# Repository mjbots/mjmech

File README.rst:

======
mjmech
======

Source and design files for various walking robots, their controlling
interfaces, and utilities for developing and operating them.

* GitHub https://github.com/mjbots/mjmech
* Most files are free hardware and software: Apache 2.0 License

Directory structure
===================

 * **base/** - C++ source files common to many applications.
 * **mech/** - C++ source files specific to walking robots.
 * **python/** - Python bindings for various C++ classes.
 * **legtool/** - A python application for experimenting with static
   walking gaits.
 * **tools/** - Utilities for development and data analysis.
 * **video-ui/** - Client application for FPV and real-time control.
 * **configs/** - Configuration files for different robots and applications.
 * **hw/** - Hardware design files along with firmware.

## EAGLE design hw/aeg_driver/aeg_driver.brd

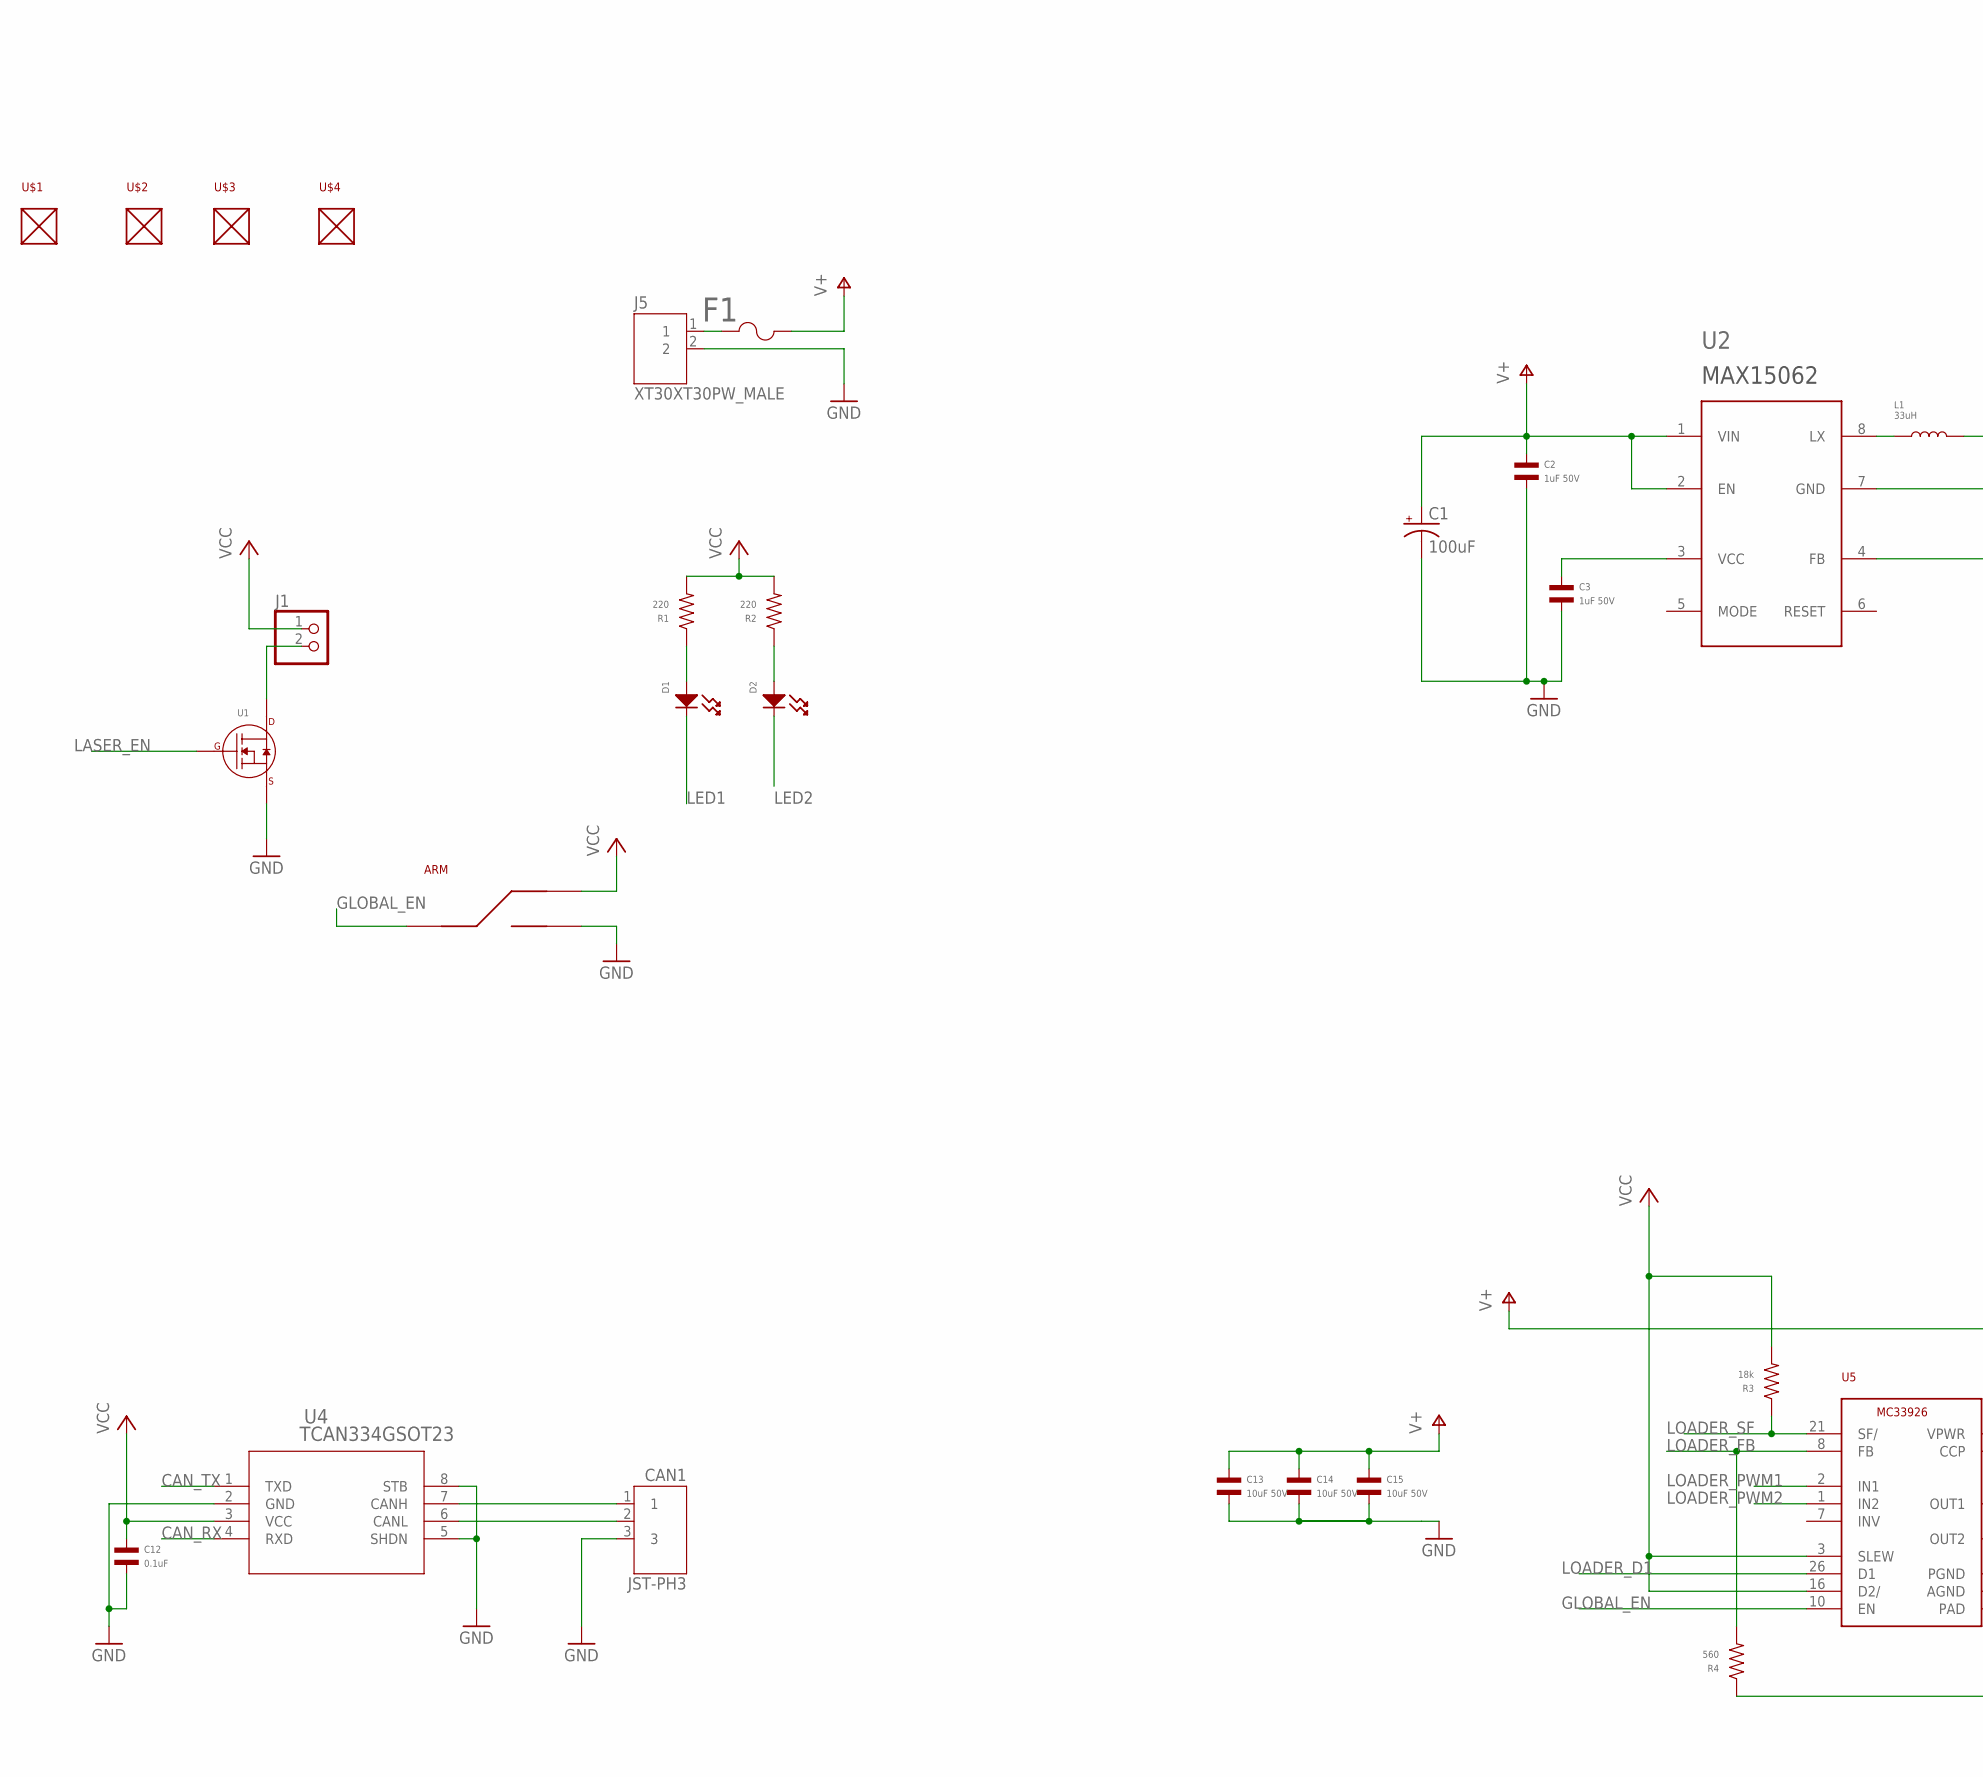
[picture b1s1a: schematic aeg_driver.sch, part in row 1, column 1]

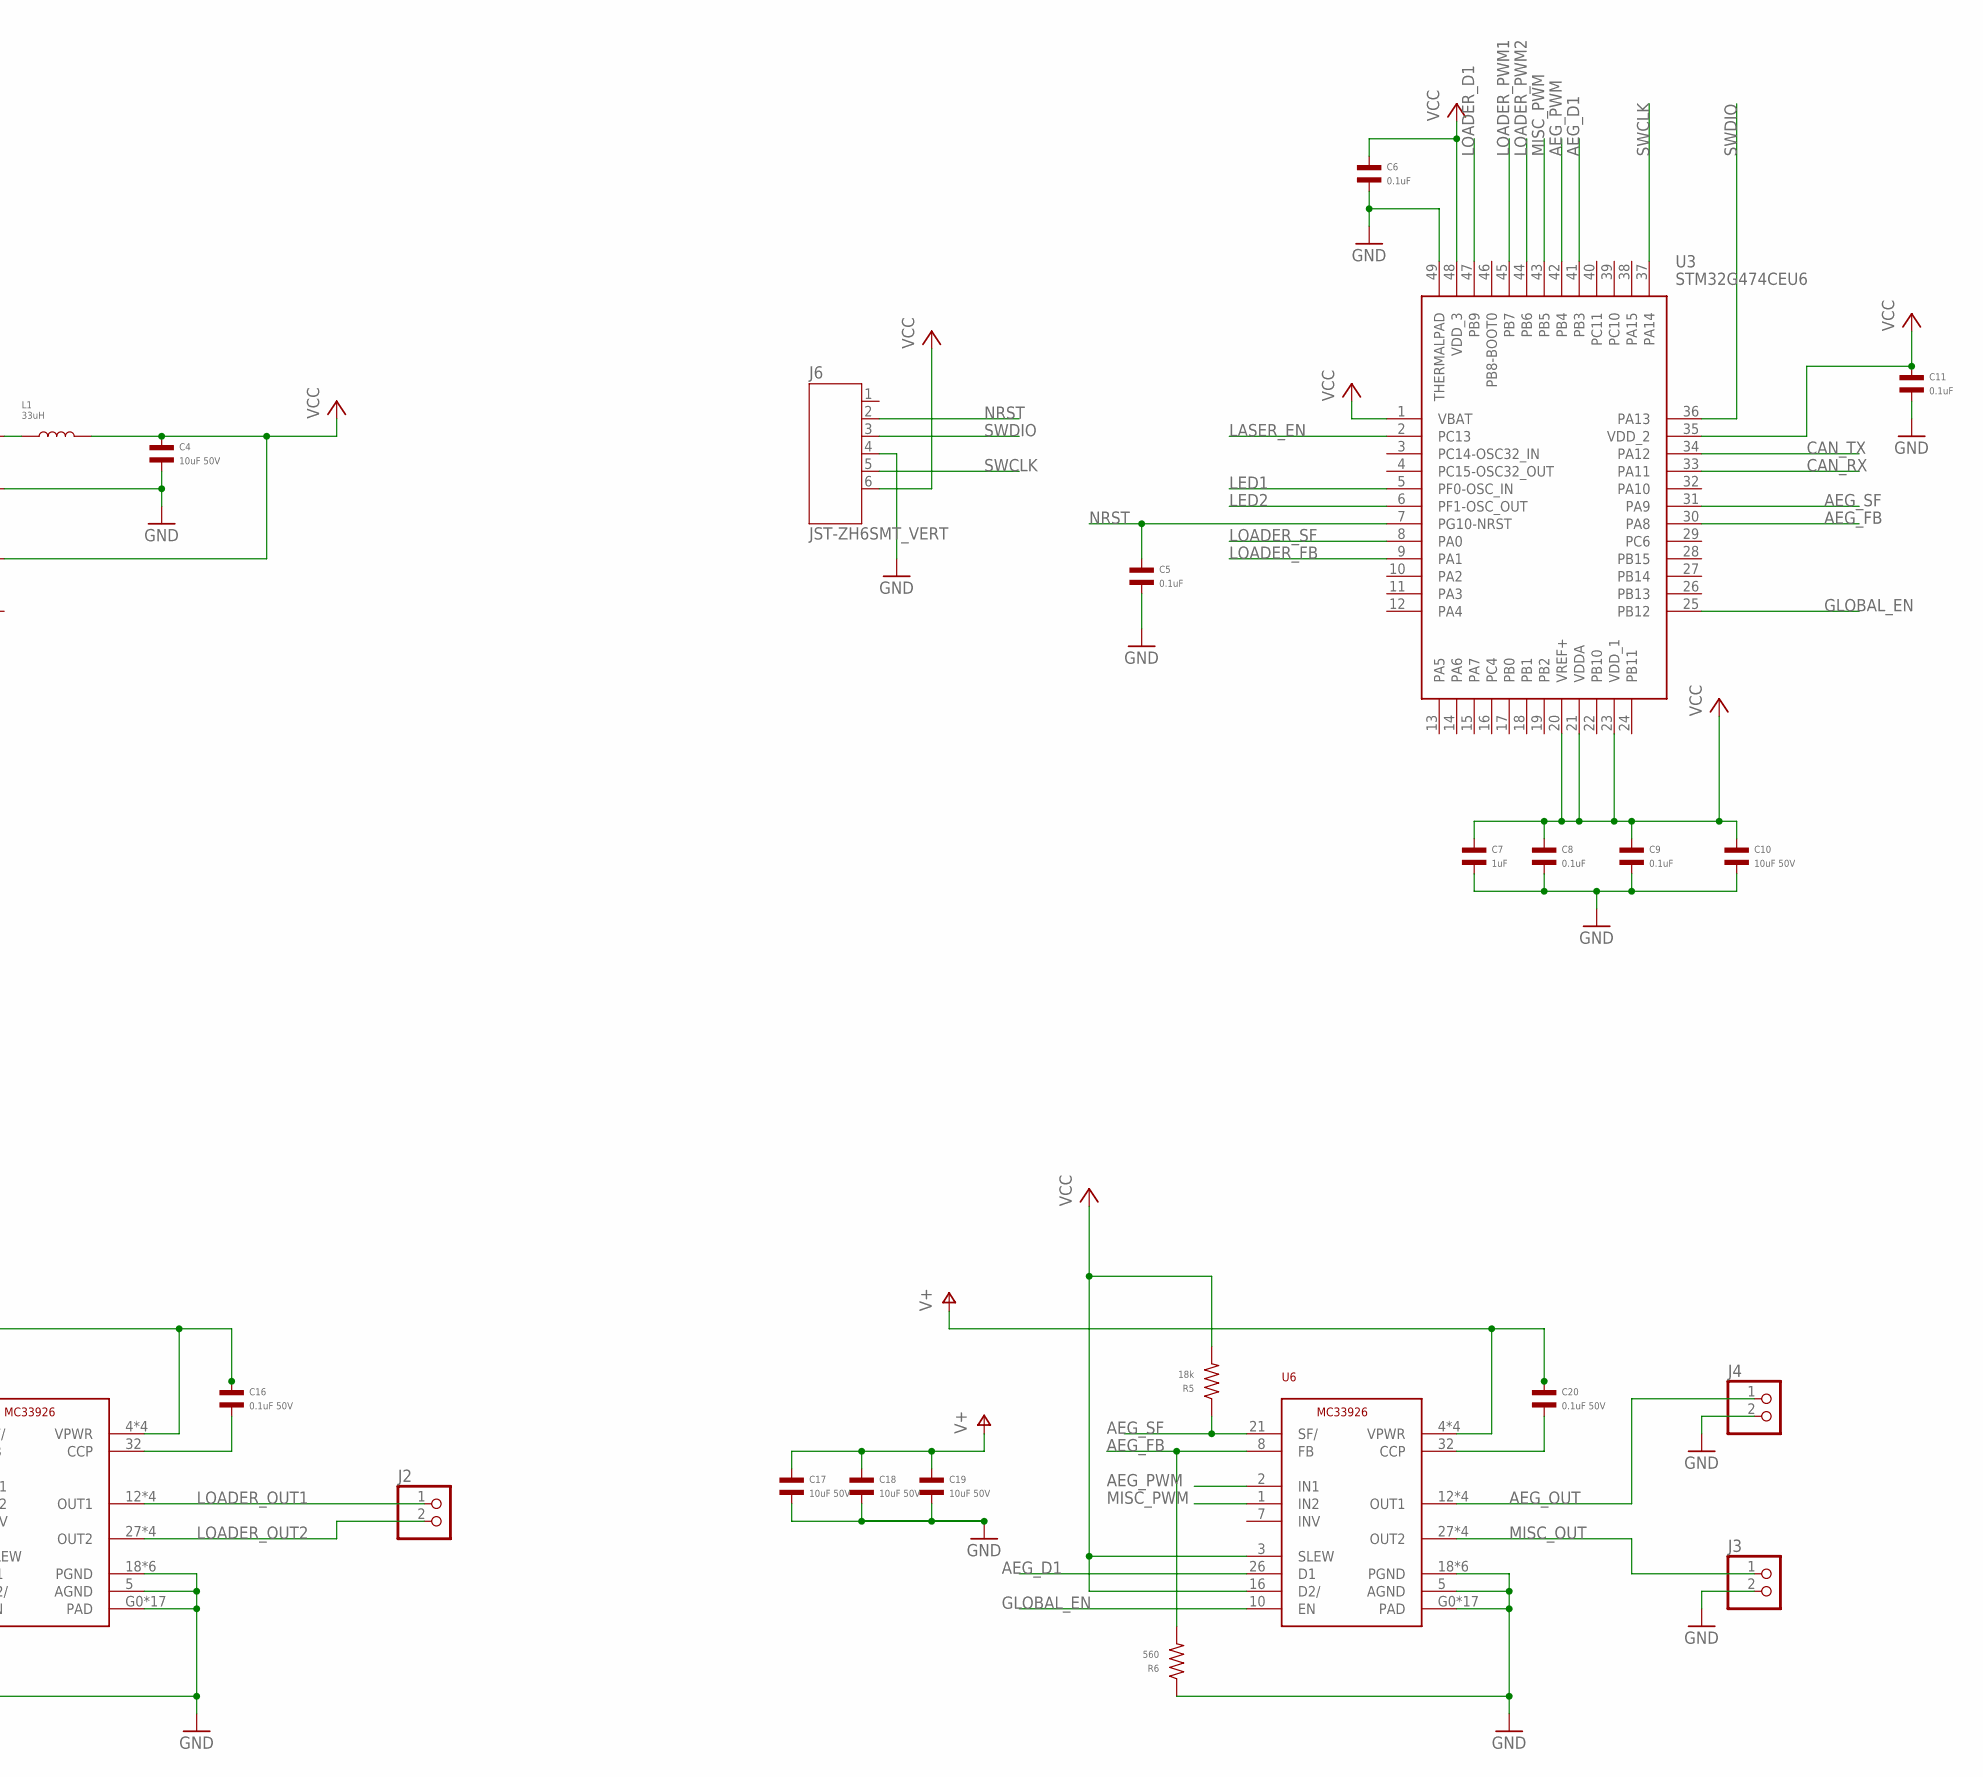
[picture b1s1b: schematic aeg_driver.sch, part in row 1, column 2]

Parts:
ARM: SLIDE_SWITCHJS_SUB_SWITCH; JS_SUB_SWITCH; MPN JS102011SAQN
C1: 100uF; PANASONIC_FT_CAP_D; MPN EEE-FT1V101AP
C2, C3: 1uF 50V; C0603; MPN CL10A105KB8NNNC
C4, C10, C13, C14, C15, C17, C18, C19: 10uF 50V; C1206; MPN C3216X7R1H106K160AE
C5, C6, C8, C9, C11, C12: 0.1uF; C0402; MPN MF-CAP-0402-0.1uF
C7: 1uF; C0402; MPN MF-CAP-0402-1uF
C16, C20: 0.1uF 50V; C0402; MPN 0402B104K500CT
CAN1: JST-PH3; JST_S3B-PH-SM4-TB(LF)(SN); MPN S3B-PH-SM4-TB(LF)(SN)
D1: LED_SINGLE-0603-RED; LED0603
D2: LED_SINGLE-0603-RED; LED0603; MPN MF-LED-0603-GREEN
F1: MFU0603FF04000P100; FUS_VISHAY_MFU0603; MPN MFU0603FF04000P100
J1, J2, J3, J4: PINHD-1X2; 1X02
J5: XT30XT30PW_MALE; XT30PW_MALE; MPN XT30PW-M
J6: JST-ZH6SMT_VERT; JST_B6B-ZR-SM4-TF(LF)(SN); MPN B6B-ZR-SM4-TF(LF)(SN)
L1: 33uH; L1210; MPN NLFV32T-330K-EF
R1, R2: 220; R0603; MPN MF-RES-0603-220
R3, R5: 18k; R0603; MPN MF-RES-0603-18K
R4, R6: 560; R0603; MPN MF-RES-0603-560
U1: N-CHANNEL_FET_SOT-23-3; SOT-23-3; MPN MF-DSC-SOT233-BSS138
U2: MAX150628TDFN; 8TDFN; MPN MAX15062AATA+T
U3: STM32G474CEU6; QFN50P700X700X60-49N; MPN STM32G474CEU6
U4: TCAN334GSOT23; SOT23-8; MPN TCAN334GDCNT
U5, U6: MC33926; PQFN32; MPN MC33926PNBR2
U$1, U$2, U$3, U$4: MOUNT; M2.5MOUNT

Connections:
AEG_D1: U3.41 (PB3), U6.26 (D1)
AEG_FB: R6.P$2, U3.30 (PA8), U6.8 (FB)
AEG_OUT: J4.1, U6.12 (OUT1), U6.13 (OUT1), U6.14 (OUT1), U6.15 (OUT1)
AEG_PWM: U3.42 (PB4), U6.2 (IN1)
AEG_SF: R5.P$1, U3.31 (PA9), U6.21 (SF/)
CAN_N: CAN1.2, U4.6 (CANL)
CAN_P: CAN1.1, U4.7 (CANH)
CAN_RX: U3.33 (PA11), U4.4 (RXD)
CAN_TX: U3.34 (PA12), U4.1 (TXD)
GLOBAL_EN: ARM.2, U3.25 (PB12), U5.10 (EN), U6.10 (EN)
GND: ARM.3, C1.-, C2.P$2, C3.P$2, C4.P$2, C5.P$2, C6.P$2, C7.P$2, C8.P$2, C9.P$2, C10.P$2, C11.P$2, C12.P$2, C13.P$2, C14.P$2, C15.P$2, C17.P$2, C18.P$2, C19.P$2, CAN1.3, J3.2, J4.2, J5.2, J6.4, R4.P$1, R6.P$1, U1.P$2 (SOURCE), U2.7 (GND), U3.49 (THERMALPAD), U4.2 (GND), U4.5 (SHDN), U4.8 (STB), U5.5 (AGND), U5.18 (PGND), U5.19 (PGND), U5.20 (PGND), U5.22 (PGND), U5.23 (PGND), U5.24 (PGND), U5.G0 (PAD), U5.G1 (PAD), U5.G2 (PAD), U5.G3 (PAD), U5.G4 (PAD), U5.G5 (PAD), U5.G6 (PAD), U5.G7 (PAD), U5.G8 (PAD), U5.G9 (PAD), U5.G10 (PAD), U5.G11 (PAD), U5.G12 (PAD), U5.G13 (PAD), U5.G14 (PAD), U5.G15 (PAD), U5.G16 (PAD), U6.5 (AGND), U6.18 (PGND), U6.19 (PGND), U6.20 (PGND), U6.22 (PGND), U6.23 (PGND), U6.24 (PGND), U6.G0 (PAD), U6.G1 (PAD), U6.G2 (PAD), U6.G3 (PAD), U6.G4 (PAD), U6.G5 (PAD), U6.G6 (PAD), U6.G7 (PAD), U6.G8 (PAD), U6.G9 (PAD), U6.G10 (PAD), U6.G11 (PAD), U6.G12 (PAD), U6.G13 (PAD), U6.G14 (PAD), U6.G15 (PAD), U6.G16 (PAD)
LASER_EN: U1.P$1 (GATE), U3.2 (PC13)
LED1: D1.CATHODE, U3.5 (PF0-OSC_IN)
LED2: D2.CATHODE, U3.6 (PF1-OSC_OUT)
LOADER_D1: U3.47 (PB9), U5.26 (D1)
LOADER_FB: R4.P$2, U3.9 (PA1), U5.8 (FB)
LOADER_OUT1: J2.1, U5.12 (OUT1), U5.13 (OUT1), U5.14 (OUT1), U5.15 (OUT1)
LOADER_OUT2: J2.2, U5.27 (OUT2), U5.28 (OUT2), U5.29 (OUT2), U5.30 (OUT2)
LOADER_PWM1: U3.45 (PB7), U5.2 (IN1)
LOADER_PWM2: U3.44 (PB6), U5.1 (IN2)
LOADER_SF: R3.P$1, U3.8 (PA0), U5.21 (SF/)
LX: L1.P$1, U2.8 (LX)
MISC_OUT: J3.1, U6.27 (OUT2), U6.28 (OUT2), U6.29 (OUT2), U6.30 (OUT2)
MISC_PWM: U3.43 (PB5), U6.1 (IN2)
unnamed: C20.P$2, U6.32 (CCP)
unnamed: J1.2, U1.P$3 (DRAIN)
unnamed: F1.1, J5.1
unnamed: C16.P$2, U5.32 (CCP)
unnamed: C3.P$1, U2.3 (VCC)
unnamed: D1.ANODE, R1.P$1
unnamed: D2.ANODE, R2.P$1
NRST: C5.P$1, J6.2, U3.7 (PG10-NRST)
SWCLK: J6.5, U3.37 (PA14)
SWDIO: J6.3, U3.36 (PA13)
V+: C1.+, C2.P$1, C13.P$1, C14.P$1, C15.P$1, C16.P$1, C17.P$1, C18.P$1, C19.P$1, C20.P$1, F1.2, U2.1 (VIN), U2.2 (EN), U5.4 (VPWR), U5.6 (VPWR), U5.11 (VPWR), U5.31 (VPWR), U6.4 (VPWR), U6.6 (VPWR), U6.11 (VPWR), U6.31 (VPWR)
VCC: ARM.1, C4.P$1, C6.P$1, C7.P$1, C8.P$1, C9.P$1, C10.P$1, C11.P$1, C12.P$1, J1.1, J6.6, L1.P$2, R1.P$2, R2.P$2, R3.P$2, R5.P$2, U2.4 (FB), U3.1 (VBAT), U3.20 (VREF+), U3.21 (VDDA), U3.23 (VDD_1), U3.35 (VDD_2), U3.48 (VDD_3), U4.3 (VCC), U5.3 (SLEW), U5.16 (D2/), U6.3 (SLEW), U6.16 (D2/)

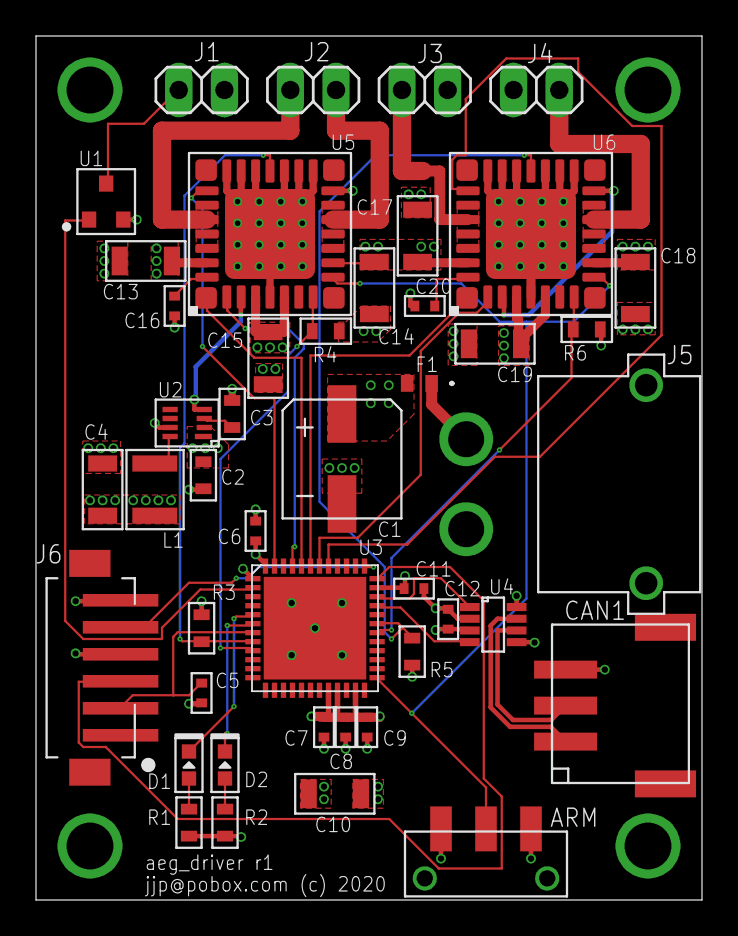
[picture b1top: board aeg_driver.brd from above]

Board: 4 copper layers, 37.0 x 48.0 mm, 48 parts (0 on the bottom side), 36 nets.

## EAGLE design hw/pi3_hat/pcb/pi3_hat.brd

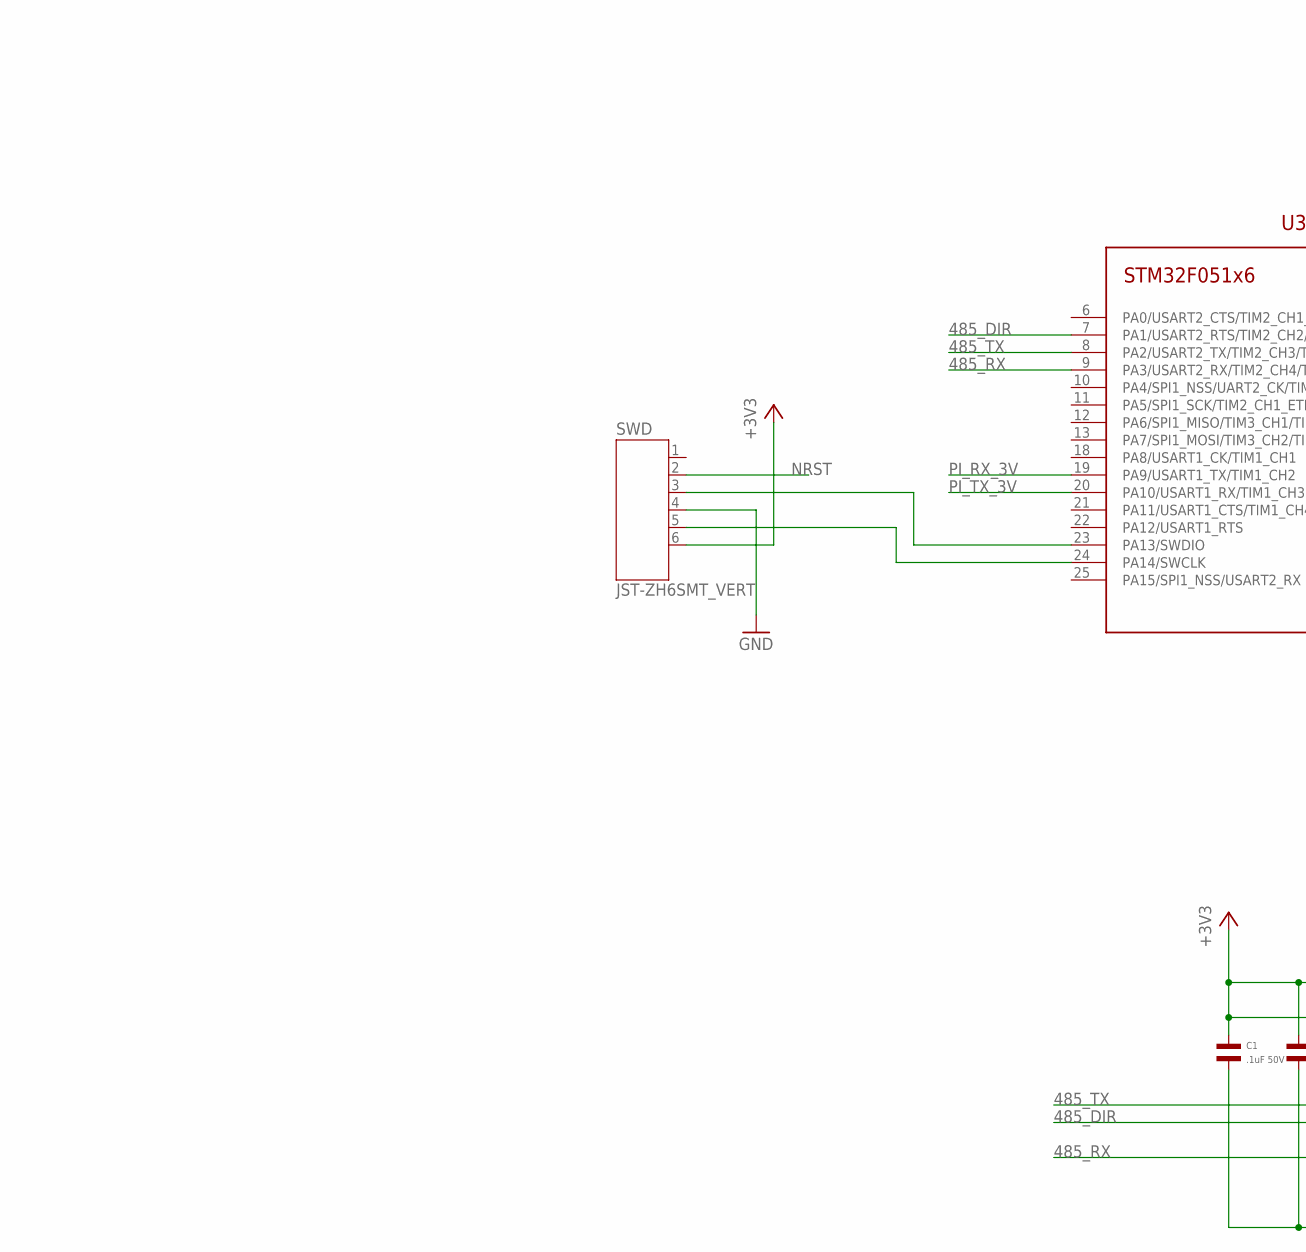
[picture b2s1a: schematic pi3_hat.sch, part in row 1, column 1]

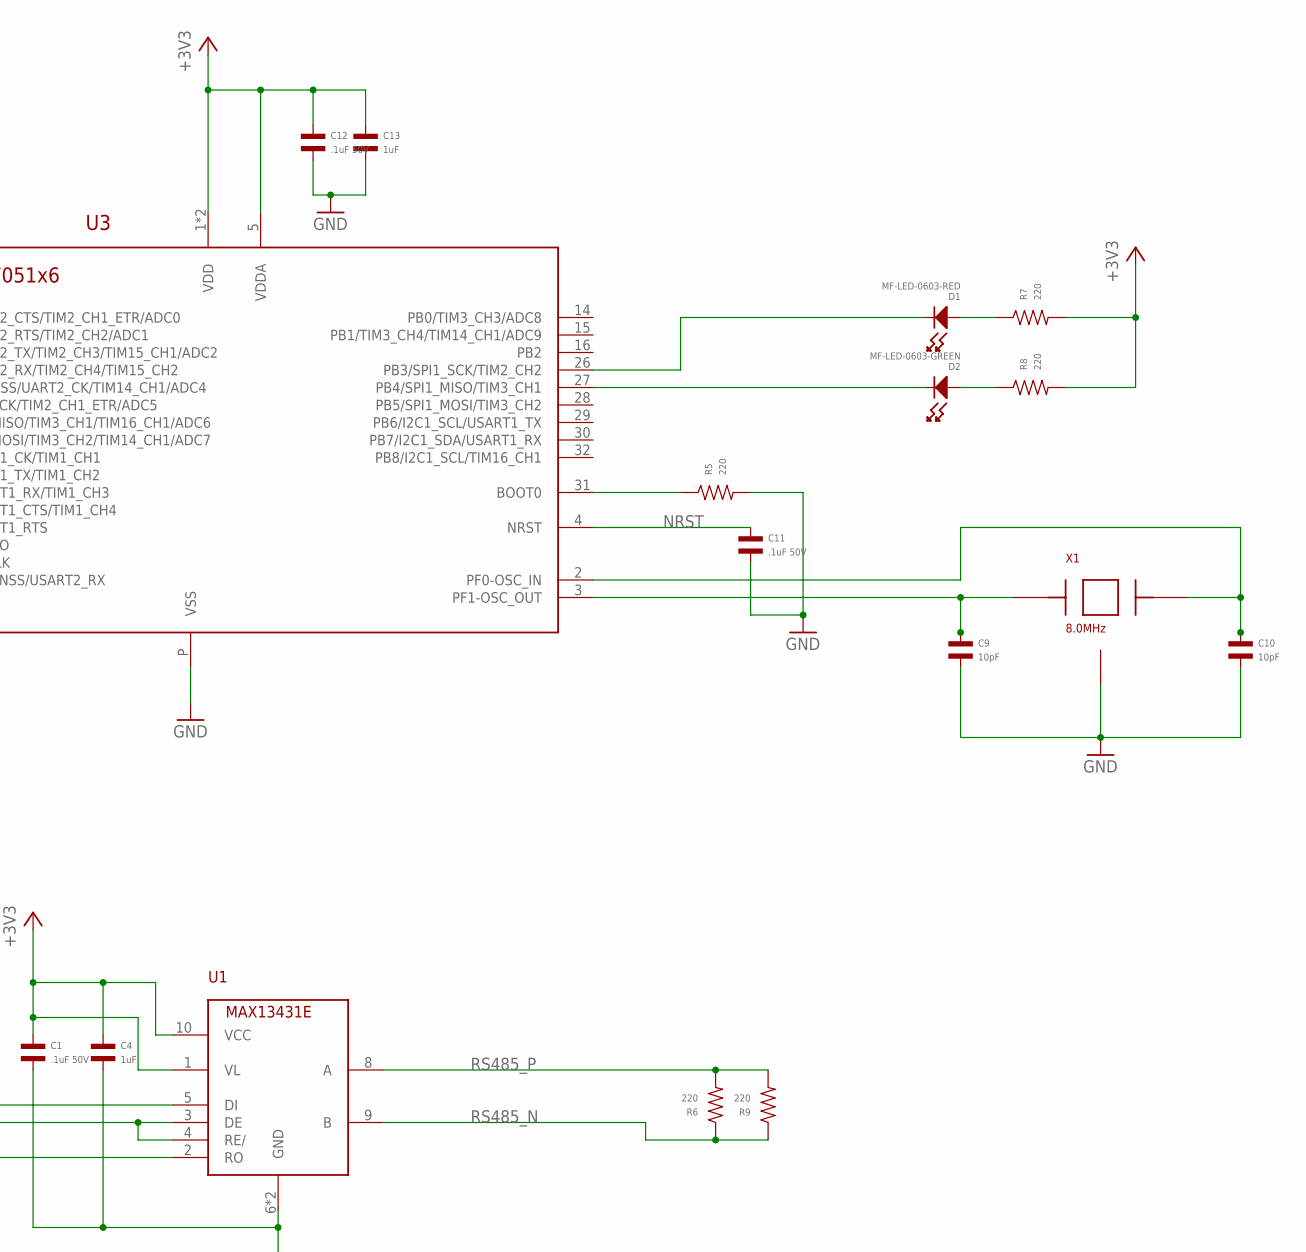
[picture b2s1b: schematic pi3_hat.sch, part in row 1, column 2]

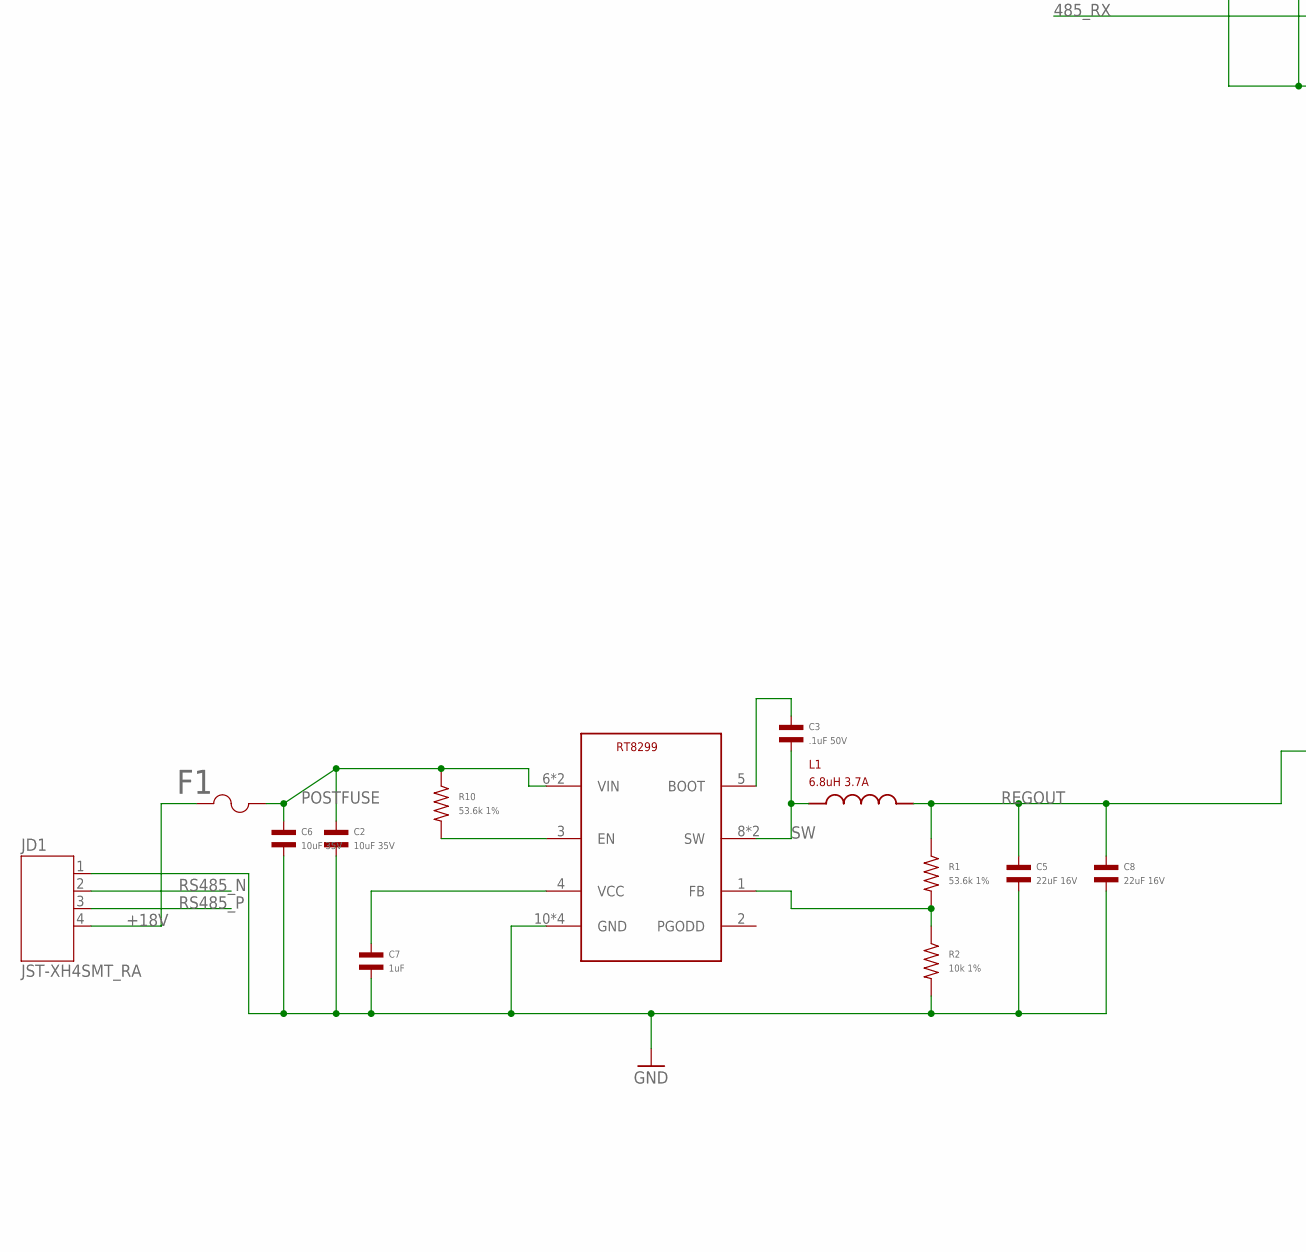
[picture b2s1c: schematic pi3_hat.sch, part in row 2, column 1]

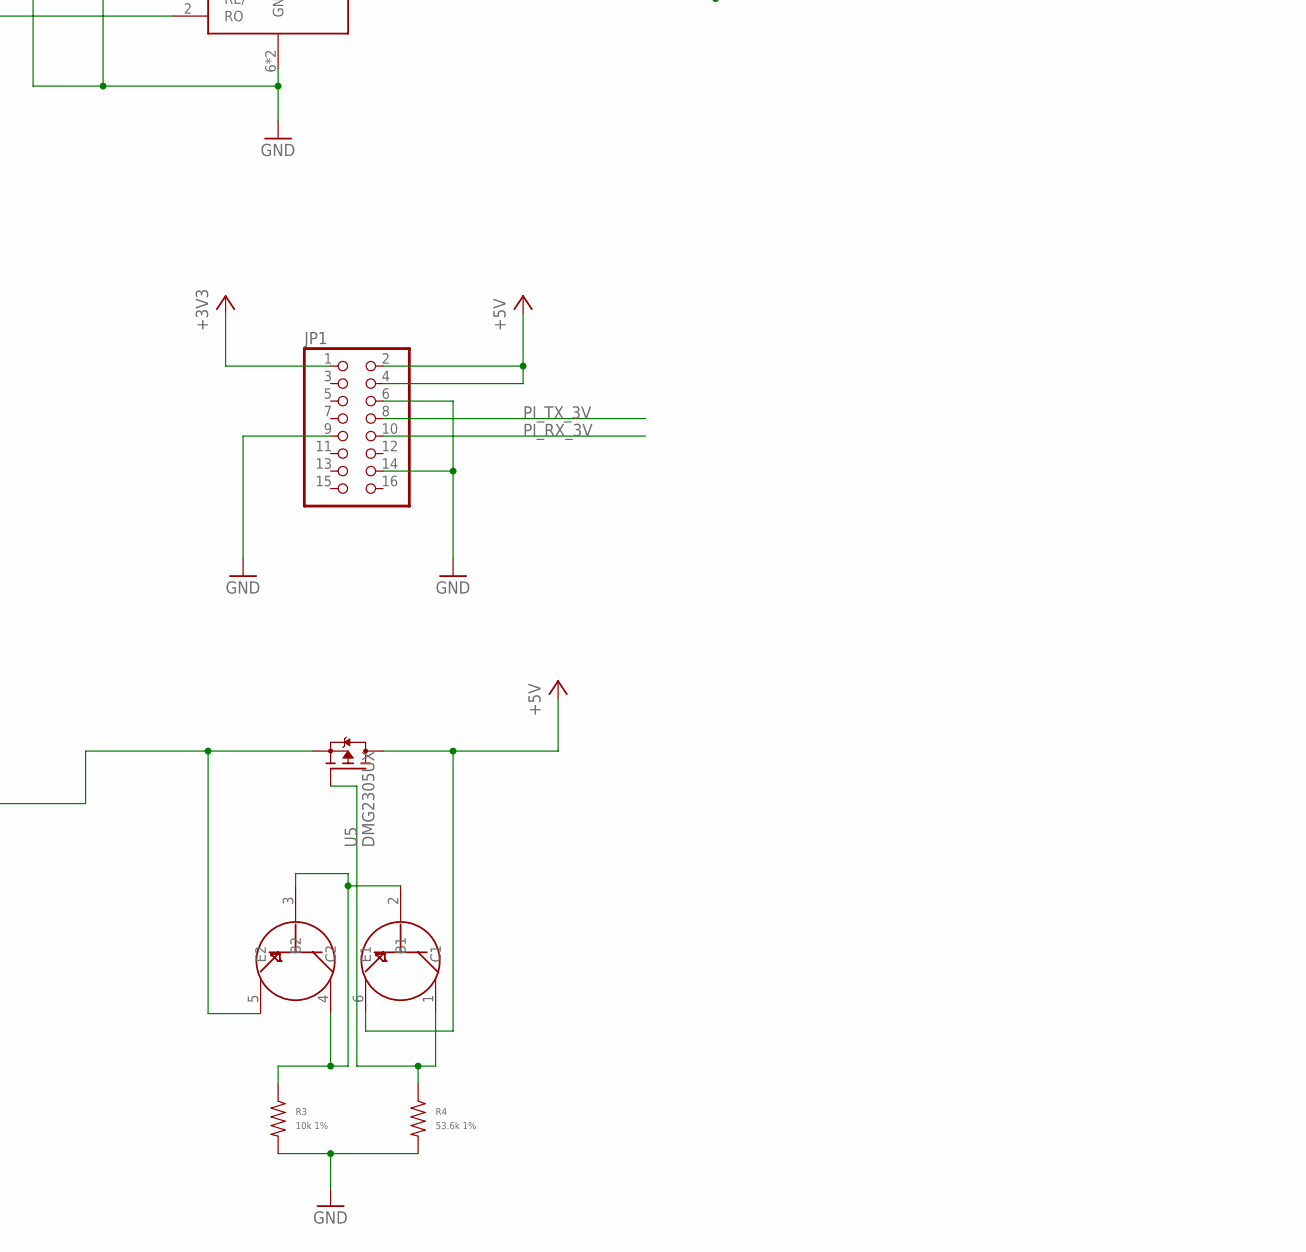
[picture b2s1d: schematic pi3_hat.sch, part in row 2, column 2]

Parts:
C1, C3, C11, C12: .1uF 50V; C0805; MPN MF-CAP-0805-0.1uF
C2, C6: 10uF 35V; C1206; MPN CGA5L1X7R1V106K160AC
C4, C7, C13: 1uF; C0603; MPN MF-CAP-0603-1uF
C5, C8: 22uF 16V; C1210; MPN CL32A226KOJNNNE
C9, C10: 10pF; C0603; MPN MF-CAP-0603-10pF
D1: MF-LED-0603-RED; LED0603
D2: MF-LED-0603-GREEN; LED0603
F1: MFU0603FF04000P100; FUS_VISHAY_MFU0603; MPN MFU0603FF04000P100
JD1: JST-XH4SMT_RA; JST_XH_SMT_RA_4; MPN S4B-XH-SM4-TB(LF)(SN)
JP1: PINHD-2X8; 2X08
L1: 6.8uH 3.7A; TAIYO_8040; MPN NR8040T6R8N
R1, R4, R10: 53.6k 1%; R0603; MPN ERJ-3EKF5362V
R2, R3: 10k 1%; R0603; MPN ERJ-3EKF1002V
R5, R6, R7, R8, R9: 220; R0603; MPN MF-RES-0603-220
SWD: JST-ZH6SMT_VERT; JST_B6B-ZR-SM4-TF(LF)(SN); MPN B6B-ZR-SM4-TF(LF)(SN)
U1: MAX13431E; TDFN10; MPN MAX13431EETB+T
U2: RT829910L_DFN; 10L_DFN
U3: STM32F051X6UFQFPN32; UFQFPN32; MPN STM32F051K6U6
U4: DMMT5401; SOT26; MPN DMMT5401-7-F
U5: DMG2305UX; SOT23; MPN DMG2305UX-13
X1: 8.0MHz; ABM3B; MPN ABM3B-8.000MHZ-10-1-U-T

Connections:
485_DIR: U1.3 (DE), U1.4 (RE/), U3.7 (PA1/USART2_RTS/TIM2_CH2/ADC1)
485_RX: U1.2 (RO), U3.9 (PA3/USART2_RX/TIM2_CH4/TIM15_CH2)
485_TX: U1.5 (DI), U3.8 (PA2/USART2_TX/TIM2_CH3/TIM15_CH1/ADC2)
+3V3: C1.P$1, C4.P$1, C12.P$1, C13.P$1, JP1.1, R7.P$2, R8.P$2, SWD.6, U1.1 (VL), U1.10 (VCC), U3.1 (VDD), U3.5 (VDDA), U3.17 (VDD)
+5V: JP1.2, JP1.4, U4.6 (E1), U5.3 (D)
+18V: F1.1, JD1.4
GND: C1.P$2, C2.P$2, C4.P$2, C5.P$2, C6.P$2, C7.P$2, C8.P$2, C9.P$2, C10.P$2, C11.P$2, C12.P$2, C13.P$2, JD1.1, JP1.6, JP1.9, JP1.14, R2.P$2, R3.P$2, R4.P$2, R5.P$2, SWD.4, U1.6 (GND), U1.PAD (GND), U2.10 (GND), U2.P0 (GND), U2.P1 (GND), U2.P2 (GND), U3.P (VSS), X1.2, X1.4
unnamed: R3.P$1, U4.2 (B1), U4.3 (B2), U4.4 (C2)
unnamed: C7.P$1, U2.4 (VCC)
unnamed: R5.P$1, U3.31 (BOOT0)
unnamed: R4.P$1, U4.1 (C1), U5.1 (G)
unnamed: R10.P$2, U2.3 (EN)
unnamed: C3.P$1, U2.5 (BOOT)
unnamed: R1.P$2, R2.P$1, U2.1 (FB)
unnamed: SWD.5, U3.24 (PA14/SWCLK)
unnamed: SWD.3, U3.23 (PA13/SWDIO)
unnamed: D1.ANODE, R7.P$1
unnamed: D2.ANODE, R8.P$1
unnamed: D1.CATHODE, U3.26 (PB3/SPI1_SCK/TIM2_CH2)
unnamed: D2.CATHODE, U3.27 (PB4/SPI1_MISO/TIM3_CH1)
unnamed: C9.P$1, U3.3 (PF1-OSC_OUT), X1.1
unnamed: C10.P$1, U3.2 (PF0-OSC_IN), X1.3
NRST: C11.P$1, SWD.2, U3.4 (NRST)
PI_RX_3V: JP1.10, U3.19 (PA9/USART1_TX/TIM1_CH2)
PI_TX_3V: JP1.8, U3.20 (PA10/USART1_RX/TIM1_CH3)
POSTFUSE: C2.P$1, C6.P$1, F1.2, R10.P$1, U2.6 (VIN), U2.7 (VIN)
REGOUT: C5.P$1, C8.P$1, L1.2, R1.P$1, U4.5 (E2), U5.2 (S)
RS485_N: JD1.2, R6.P$1, R9.P$1, U1.9 (B)
RS485_P: JD1.3, R6.P$2, R9.P$2, U1.8 (A)
SW: C3.P$2, L1.1, U2.8 (SW), U2.9 (SW)

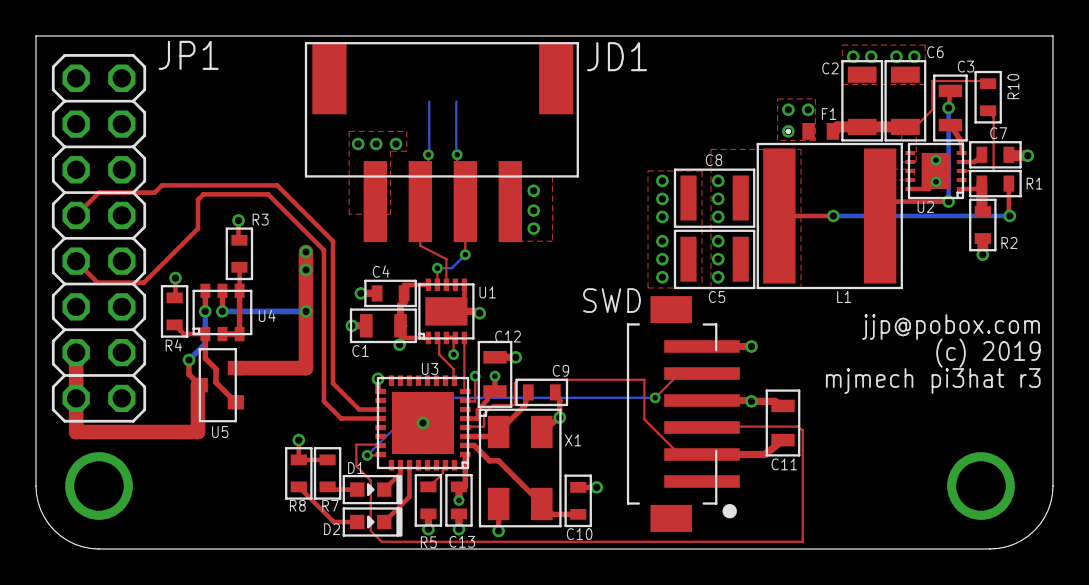
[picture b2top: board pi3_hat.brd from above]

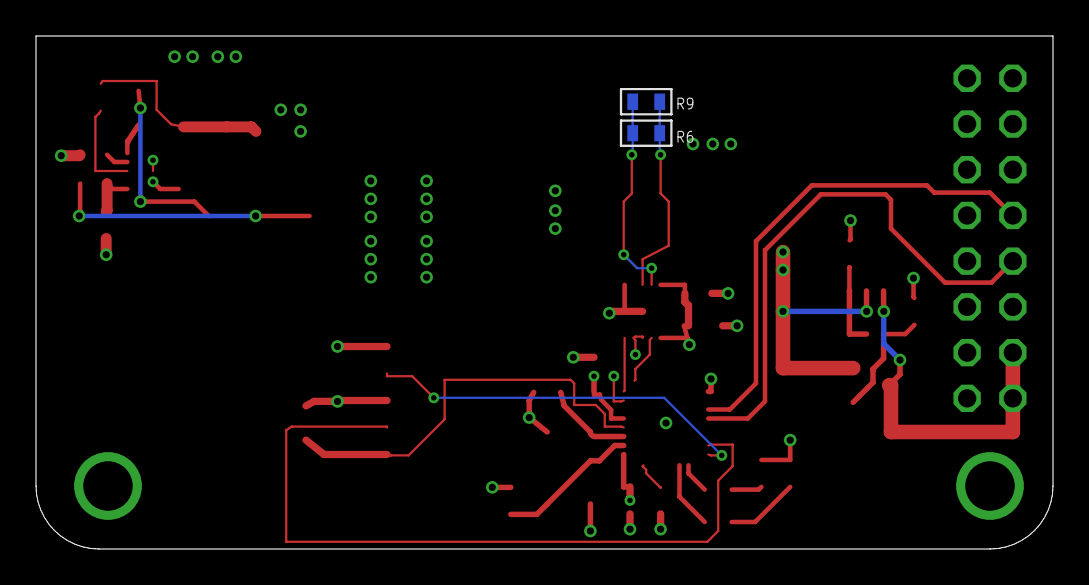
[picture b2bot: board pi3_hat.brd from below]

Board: 4 copper layers, 56.5 x 28.5 mm, 36 parts (2 on the bottom side), 30 nets.

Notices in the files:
hw/aeg_driver/aeg_driver.brd:
jjp@pobox.com (c) 2020
hw/aeg_driver/aeg_driver.sch:
(c) 2020 jjp@pobox.com
Licensed under the Apache 2.0 License
hw/gimbal/pcb/gimbal.brd:
(c) 2019
hw/joule_shield_v1/pcb/joule_shield.brd:
(c) 2017 jjp@pobox.com
hw/pressure_foot/pcb/v2/pressure_foot.brd:
(c) 2014
scoring/panel/pcb/target.brd:
v2 (c) 2015
parts and their libraries:
SparkFun-Sensors: Licensing: Creative Commons ShareAlike 4.0 International - https://creativecommons.org/licenses/by-sa/4.0
